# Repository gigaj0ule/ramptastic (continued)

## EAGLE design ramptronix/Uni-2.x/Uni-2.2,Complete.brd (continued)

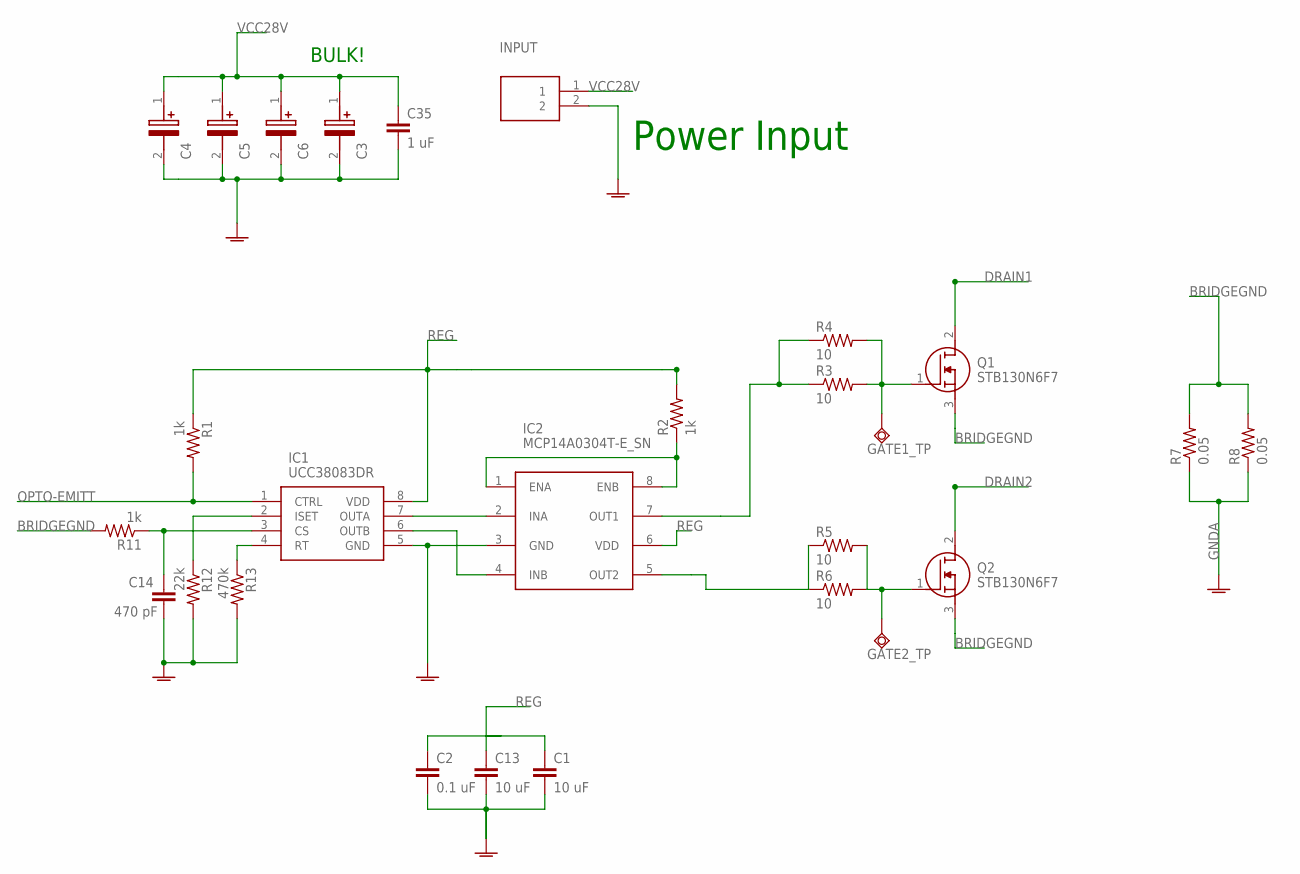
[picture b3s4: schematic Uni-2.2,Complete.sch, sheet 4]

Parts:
C1, C13: 10 uF; C0603K; LCSC_PART C440198
C2: 0.1 uF; C0603K; LCSC_PART C440198
C3, C4, C5, C6: OVK151M1VTR-10131; 16SVF1000M
C14: 470 pF; C0603K; LCSC_PART C1620
C35: 1 uF; C0805K; LCSC_PART C440198
GATE1_TP, GATE2_TP: TPSQPAD1-17; P1-17
IC1: UCC38083DR; SOIC127P600X175-8N
IC2: MCP14A0304T-E_SN; SOIC127P600X175-8N
INPUT: TB005-762-02BE; TB00576202BE
Q1, Q2: STB130N6F7; D2PAK
R1: 1k; R0603; LCSC_PART C22975
R2: 1k; R0402
R3, R4, R5, R6: 10; R0805
R7, R8: 0.05; R2512
R11: 1k; R0603; LCSC_PART C21190
R12: 22k; R0603; LCSC_PART C31850
R13: 470k; R0603; LCSC_PART C25811

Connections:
BRIDGEGND: Q1.3 (S), Q2.3 (S), R7.2, R8.2, R11.2
CS-IN: C14.1, IC1.3 (CS), R11.1
DRAIN1: Q1.2 (D); also elsewhere on the board
DRAIN2: Q2.2 (D); also elsewhere on the board
GNDA: C1.2, C2.2, C3.2 (-), C4.2 (-), C5.2 (-), C6.2 (-), C13.2, C14.2, C35.2, IC1.5 (GND), IC2.3 (GND), INPUT.2, R7.1, R8.1, R12.2, R13.2; also elsewhere on the board
unnamed: IC1.7 (OUTA), IC2.2 (INA)
unnamed: IC1.6 (OUTB), IC2.4 (INB)
unnamed: IC2.1 (ENA), IC2.8 (ENB), R2.1
unnamed: IC2.7 (OUT1), R3.1, R4.1
unnamed: IC2.5 (OUT2), R5.1, R6.1
unnamed: IC1.2 (ISET), R12.1
OPTO-EMITT: IC1.1 (CTRL), R1.2; also elsewhere on the board
Q1G: GATE1_TP.TP, Q1.1 (G), R3.2, R4.2
Q2G: GATE2_TP.TP, Q2.1 (G), R5.2, R6.2
REG: C1.1, C2.1, C13.1, IC1.8 (VDD), IC2.6 (VDD), R1.1, R2.2; also elsewhere on the board
RT: IC1.4 (RT), R13.1
VCC28V: C3.1 (+), C4.1 (+), C5.1 (+), C6.1 (+), C35.1, INPUT.1; also elsewhere on the board

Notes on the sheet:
BULK!
Power Input

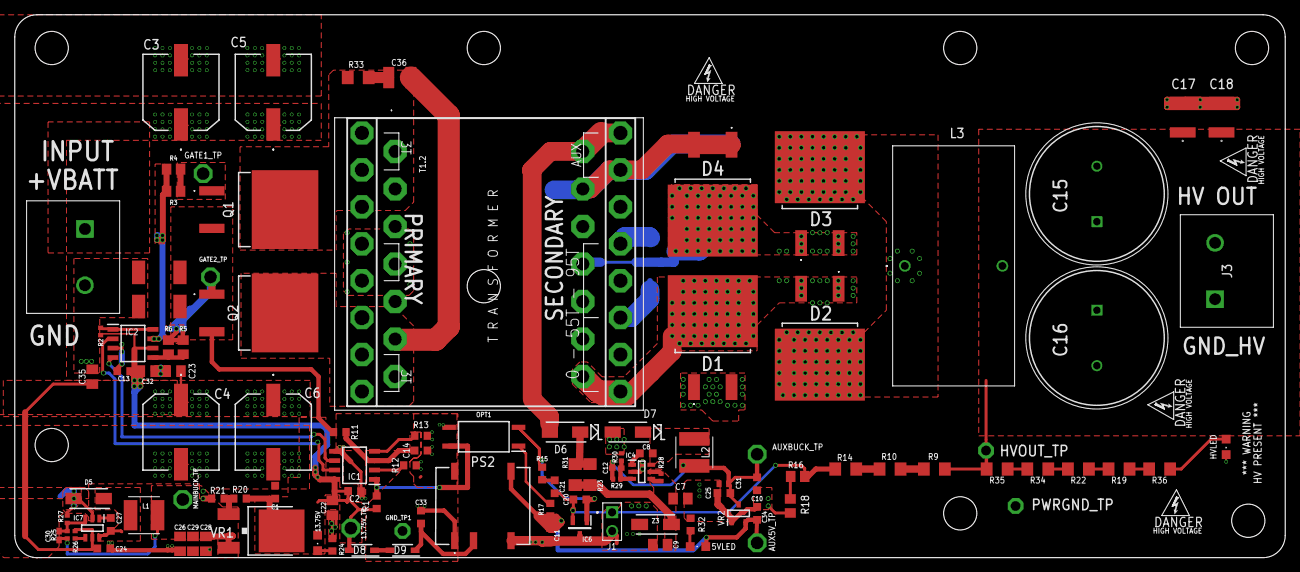
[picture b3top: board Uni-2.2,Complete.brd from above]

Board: 2 copper layers, 172.0 x 73.5 mm, 117 parts (1 on the bottom side), 56 nets.

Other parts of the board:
U$1, U$4: HV; PSFBC_ELECTRIC_SHOCK

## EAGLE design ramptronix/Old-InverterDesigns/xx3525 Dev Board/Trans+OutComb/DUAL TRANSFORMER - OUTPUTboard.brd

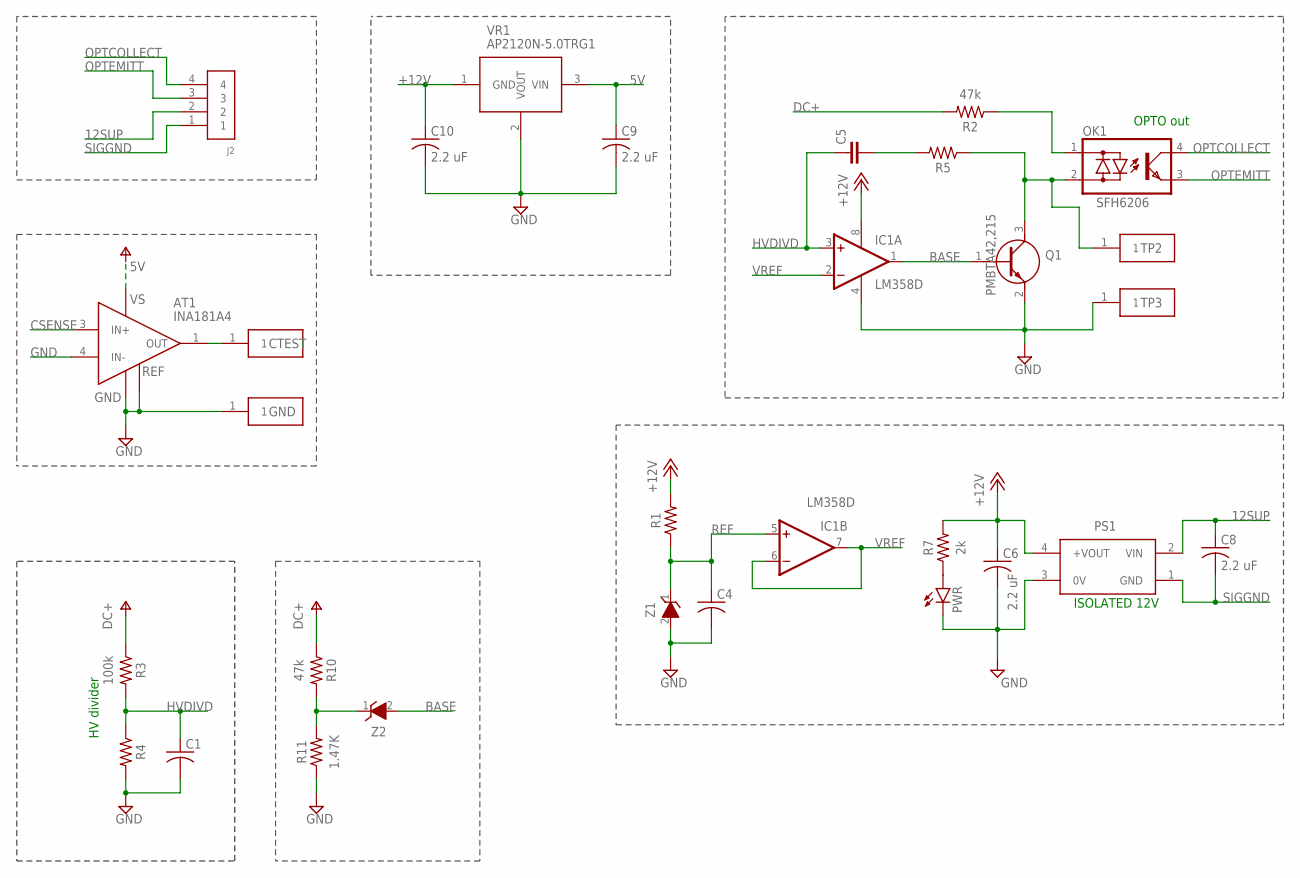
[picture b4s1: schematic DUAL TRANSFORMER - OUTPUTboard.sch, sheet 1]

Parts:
AT1: INA181A4; SOT95P280X145-6N
C1, C4: C-USC0805; C0805
C5: C-EUC0805; C0805
C6, C8, C9, C10: 2.2 uF; C0805
CTEST: RCT-0C
GND: RCT-0C
IC1: LM358D; SO08
J2: 61300411121
OK1: SFH6206; DIL4-SMD
PS1: PDSE1-S12-S3-SPDSE1S12S12S; PDSE1S12S3S
PWR: LEDSML0805; SML0805
Q1: PMBTA42,215; SOT95P230X110-3N
R1, R4, R5: R-US_CHIP-0805(2012-METRIC); RESC2012X65
R2, R10: 47k; MINI_MELF-0207R
R3: 100k; MINI_MELF-0207R
R7: 2k; RESC2012X65
R11: 1.47K; RESC2012X65
TP2, TP3: RCT-0C
VR1: AP2120N-5.0TRG1; SOT95P240X120-3N
Z1, Z2: BZT52-C5V1_R1_00001; SOD3816X135N; MOUSER_PART_NUMBER 241-BZT52C5V1

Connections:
5V: AT1.6 (VS), C9.1, VR1.3 (VIN)
12SUP: C8.1, J2.2, PS1.2 (VIN)
+12V: C6.1, C10.1, IC1.8 (V+), PS1.4 (+VOUT), R1.2, R7.2, VR1.1 (GND)
BASE: IC1.1 (OUT), Q1.1 (B), Z2.2 (A)
CSENSE: AT1.3 (IN+); also elsewhere on the board
DC+: R2.2, R3.1, R10.1; also elsewhere on the board
GND: AT1.2 (GND), AT1.4 (IN-), AT1.5 (REF), C1.2, C4.2, C6.2, C9.2, C10.2, GND.1, IC1.4 (V-), PS1.3 (0V), PWR.C, Q1.2 (E), R4.2, R11.1, TP3.1, VR1.2 (VOUT), Z1.2 (A); also elsewhere on the board
HVDIVD: C1.1, C5.1, IC1.3 (+IN), R3.2, R4.1
unnamed: PWR.A, R7.1
unnamed: R10.2, R11.2, Z2.1 (K)
unnamed: OK1.1 (AC1), R2.1
unnamed: C5.2, R5.2
unnamed: AT1.1 (OUT), CTEST.1
OPTCOLLECT: J2.4, OK1.4 (C)
OPTEMITT: J2.3, OK1.3 (E)
OPTOANODE: OK1.2 (AC2), Q1.3 (C), R5.1, TP2.1
REF: C4.1, IC1.5 (+IN), R1.1, Z1.1 (K)
SIGGND: C8.2, J2.1, PS1.1 (GND)
VREF: IC1.2 (-IN), IC1.6 (-IN), IC1.7 (OUT)

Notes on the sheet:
OPTO out
HV divider
ISOLATED 12V

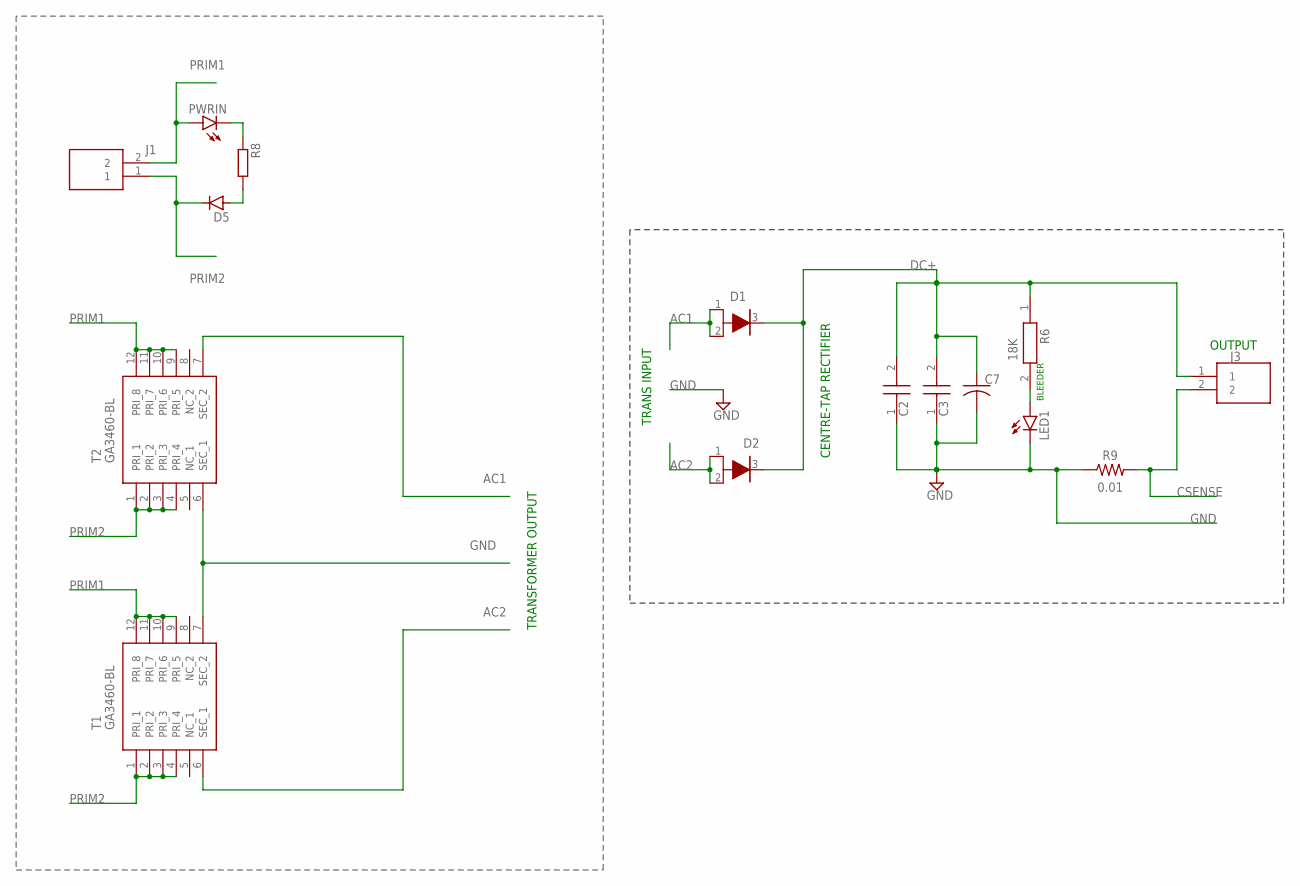
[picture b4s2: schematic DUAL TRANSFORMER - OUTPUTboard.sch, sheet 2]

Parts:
C2, C3: ELH227M400AS2AV; CAPPRD1000W140D3000H3200
C7: C-USC1210K; C1210K
D1, D2: VS-16EDH02HM3_I; V40DL45BPM3I
D5: DIODE-DO-214AC; DO-214AC
J1, J3: 2305908-2; 23059082
LED1: LED5MM
PWRIN: LEDSML0805; SML0805
R6: 18K; RESAD3100W80L1500D400
R8: R-EU_R0805; R0805
R9: 0.01; RESC6332X71
T1, T2: GA3460-BL; GA3460BL

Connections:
AC1: D1.1 (A_1), D1.2 (A), T2.7 (SEC_2)
AC2: D2.1 (A_1), D2.2 (A), T1.6 (SEC_1)
CSENSE: J3.2, R9.2; also elsewhere on the board
DC+: C2.2 (-), C3.2 (-), C7.1, D1.3 (K), D2.3 (K), J3.1, R6.1; also elsewhere on the board
GND: C2.1 (+), C3.1 (+), C7.2, LED1.K (C), R9.1, T1.7 (SEC_2), T2.6 (SEC_1); also elsewhere on the board
unnamed: D5.A, R8.2
unnamed: LED1.A, R6.2
unnamed: PWRIN.C, R8.1
PRIM1: J1.2, PWRIN.A, T1.9 (PRI_5), T1.10 (PRI_6), T1.11 (PRI_7), T1.12 (PRI_8), T2.9 (PRI_5), T2.10 (PRI_6), T2.11 (PRI_7), T2.12 (PRI_8)
PRIM2: D5.C, J1.1, T1.1 (PRI_1), T1.2 (PRI_2), T1.3 (PRI_3), T1.4 (PRI_4), T2.1 (PRI_1), T2.2 (PRI_2), T2.3 (PRI_3), T2.4 (PRI_4)

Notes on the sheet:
TRANSFORMER OUTPUT
CENTRE-TAP RECTIFIER
TRANS INPUT
OUTPUT
BLEEDER

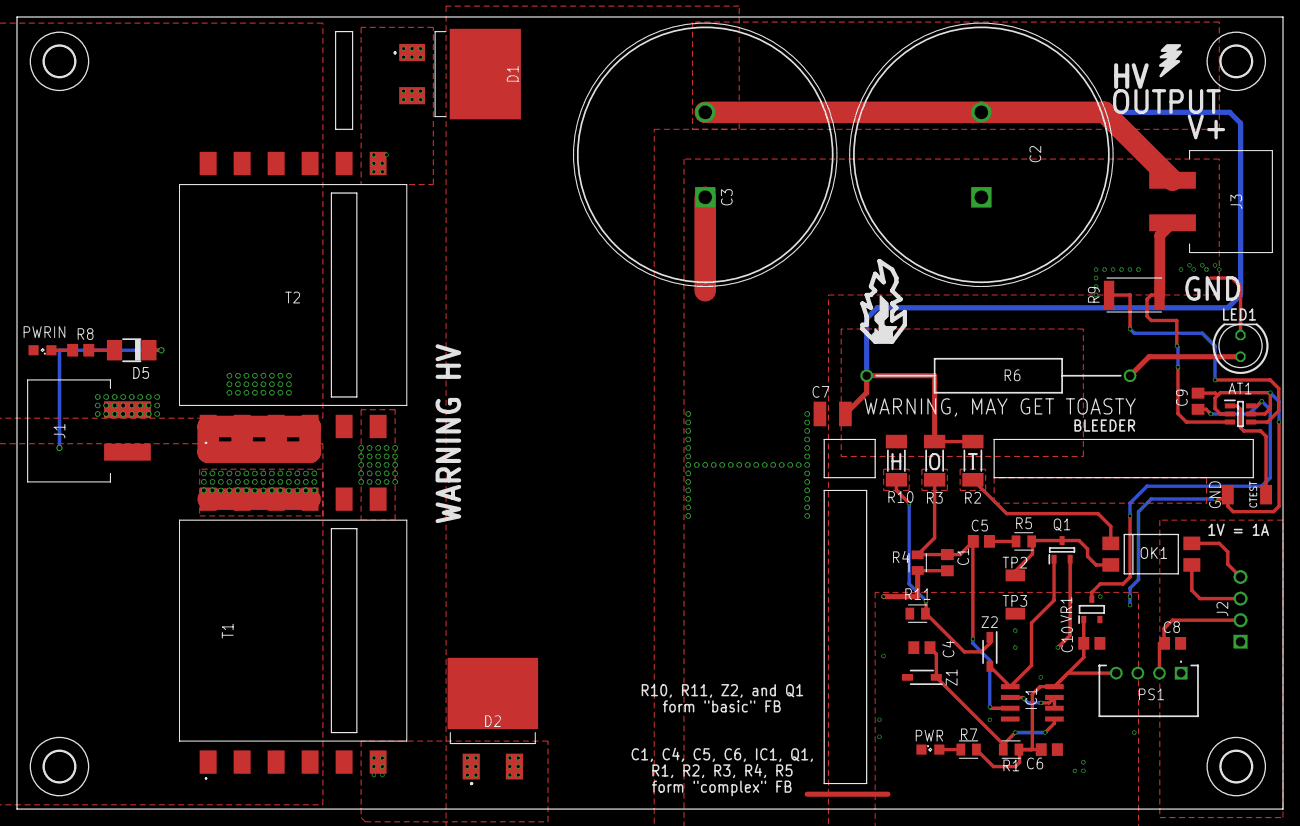
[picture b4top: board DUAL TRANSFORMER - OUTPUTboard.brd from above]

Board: 2 copper layers, 149.0 x 93.2 mm, 48 parts (0 on the bottom side), 26 nets.

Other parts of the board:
U$1, U$2, U$3, U$4: 3,6

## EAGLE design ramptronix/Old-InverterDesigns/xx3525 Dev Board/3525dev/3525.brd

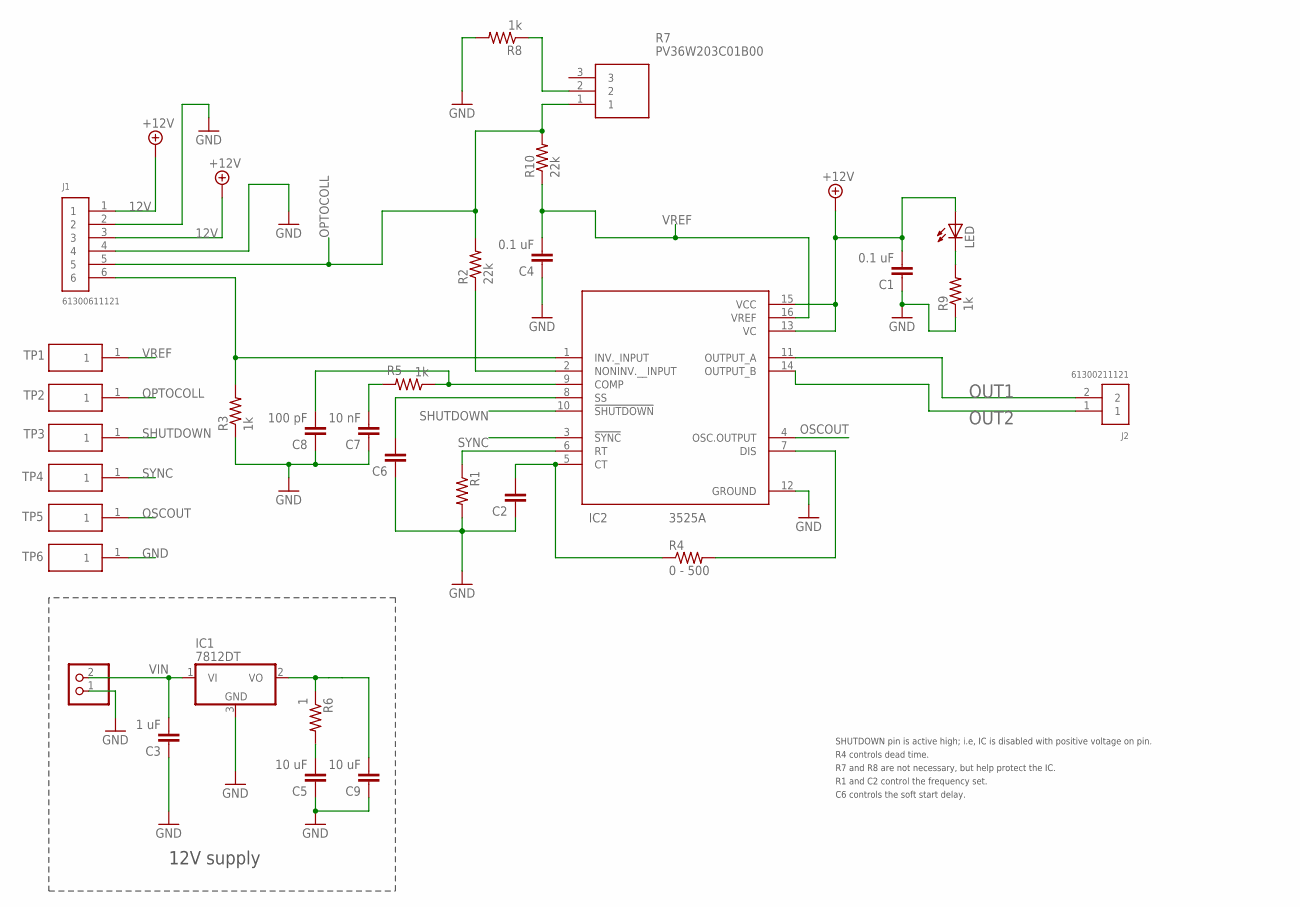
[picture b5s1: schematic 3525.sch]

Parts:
C1: 0.1 uF; C0805
C2, C6: C-EUC0805K; C0805K
C3: 1 uF; C0805K
C4: 0.1 uF; C0805K
C5, C9: 10 uF; C0805K
C7: 10 nF; C0805K
C8: 100 pF; C0805K
IC1: 7812DT; TO252
IC2: 3525A; SOIC127P1030X265-16N
J1: 61300611121
J2: 61300211121
LED: LEDCHIPLED_0805; CHIPLED_0805
R1: R-US_R0805; R0805
R2, R10: 22k; R0805
R3, R5, R8, R9: 1k; R0805
R4: 0 - 500; R0805
R6: 1; R0805
R7: PV36W203C01B00; PV36W201C01B00
SUPPLY: PINHD-1X2; 1X02
TP1, TP2, TP3, TP4, TP5, TP6: RCT-0C

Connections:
12V: C1.2, C9.2, IC1.2 (VO), IC2.13 (VC), IC2.15 (VCC), J1.1, J1.3, LED.A, R6.1
GND: C1.1, C2.1, C3.1, C4.1, C5.1, C6.1, C7.1, C8.1, C9.1, IC1.3 (GND), IC2.12 (GROUND), J1.2, J1.4, R1.2, R3.1, R8.2, R9.1, SUPPLY.1, TP6.1
unnamed: R7.2, R8.1
unnamed: C5.2, R6.2
unnamed: C8.2, IC2.9 (COMP), R5.1
unnamed: IC2.7 (DIS), R4.2
unnamed: IC2.6 (RT), R1.1
unnamed: C2.2, IC2.5 (CT), R4.1
unnamed: C6.2, IC2.8 (SS)
unnamed: LED.C, R9.2
unnamed: C7.2, R5.2
unnamed: IC2.1 (INV._INPUT), J1.6, R3.2
N-INV: IC2.2 (NONINV.__INPUT), R2.1
OPTOCOLL: J1.5, R2.2, R7.1, R10.2, TP2.1
OSCOUT: IC2.4 (OSC.OUTPUT), TP5.1
OUT1: IC2.11 (OUTPUT_A), J2.2
OUT2: IC2.14 (OUTPUT_B), J2.1
SHUTDOWN: IC2.10 (!SHUTDOWN), TP3.1
SYNC: IC2.3 (!SYNC), TP4.1
VIN: C3.2, IC1.1 (VI), SUPPLY.2
VREF: C4.2, IC2.16 (VREF), R10.1, TP1.1

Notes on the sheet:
12V supply
R4 controls dead time.
R7 and R8 are not necessary, but help protect the IC.
R1 and C2 control the frequency set.
C6 controls the soft start delay.
SHUTDOWN pin is active high; i.e, IC is disabled with positive voltage on pin.

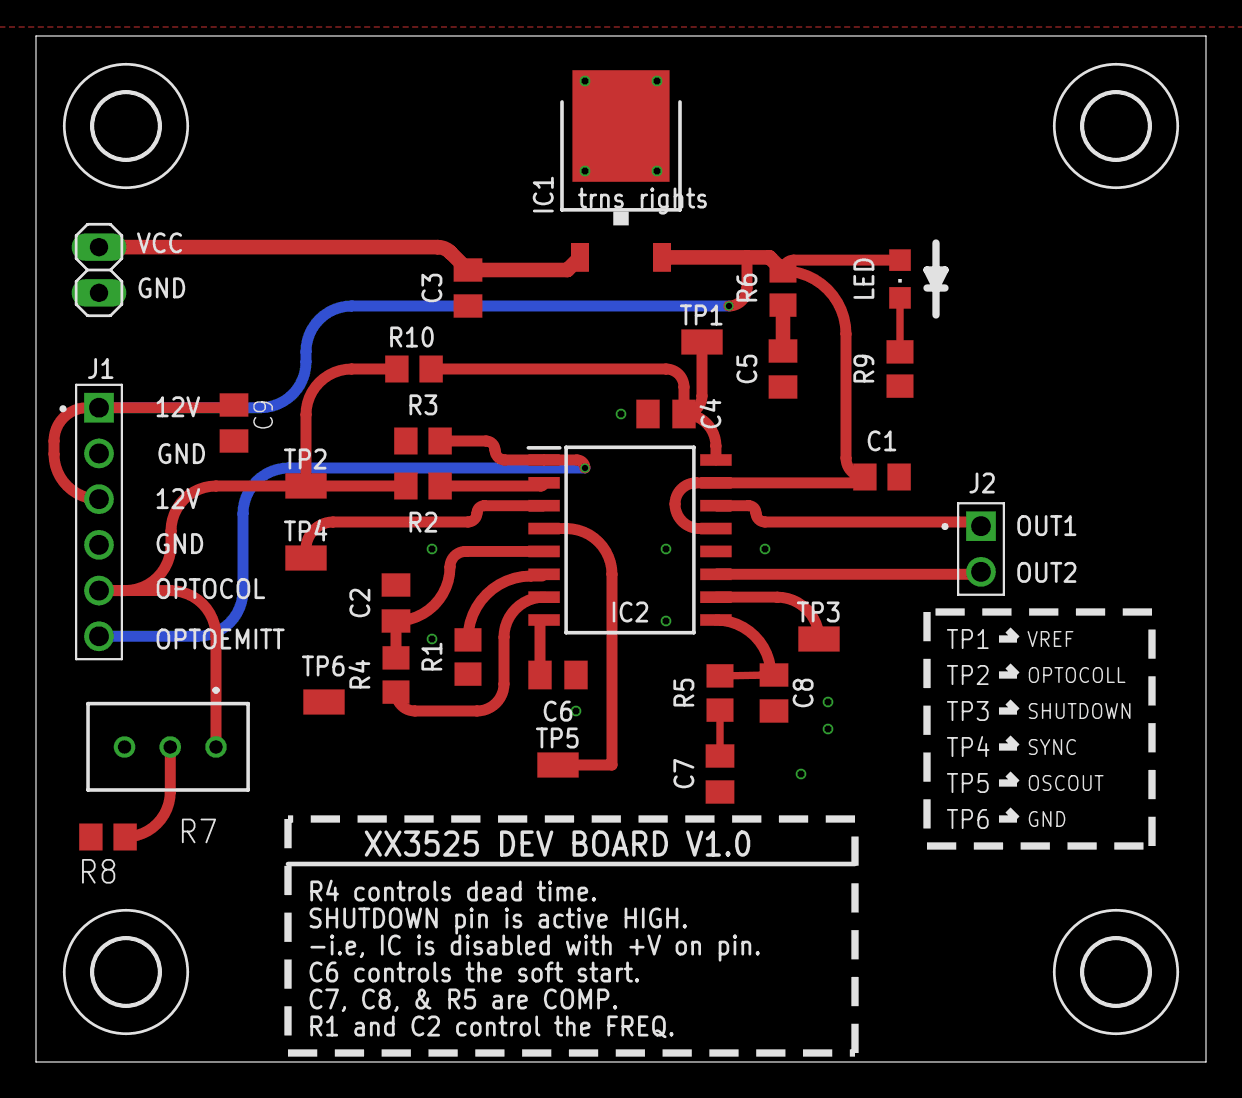
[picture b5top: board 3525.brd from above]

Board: 2 copper layers, 65.0 x 57.0 mm, 35 parts (0 on the bottom side), 21 nets.

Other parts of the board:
U$1, U$2, U$3, U$4: 3,6

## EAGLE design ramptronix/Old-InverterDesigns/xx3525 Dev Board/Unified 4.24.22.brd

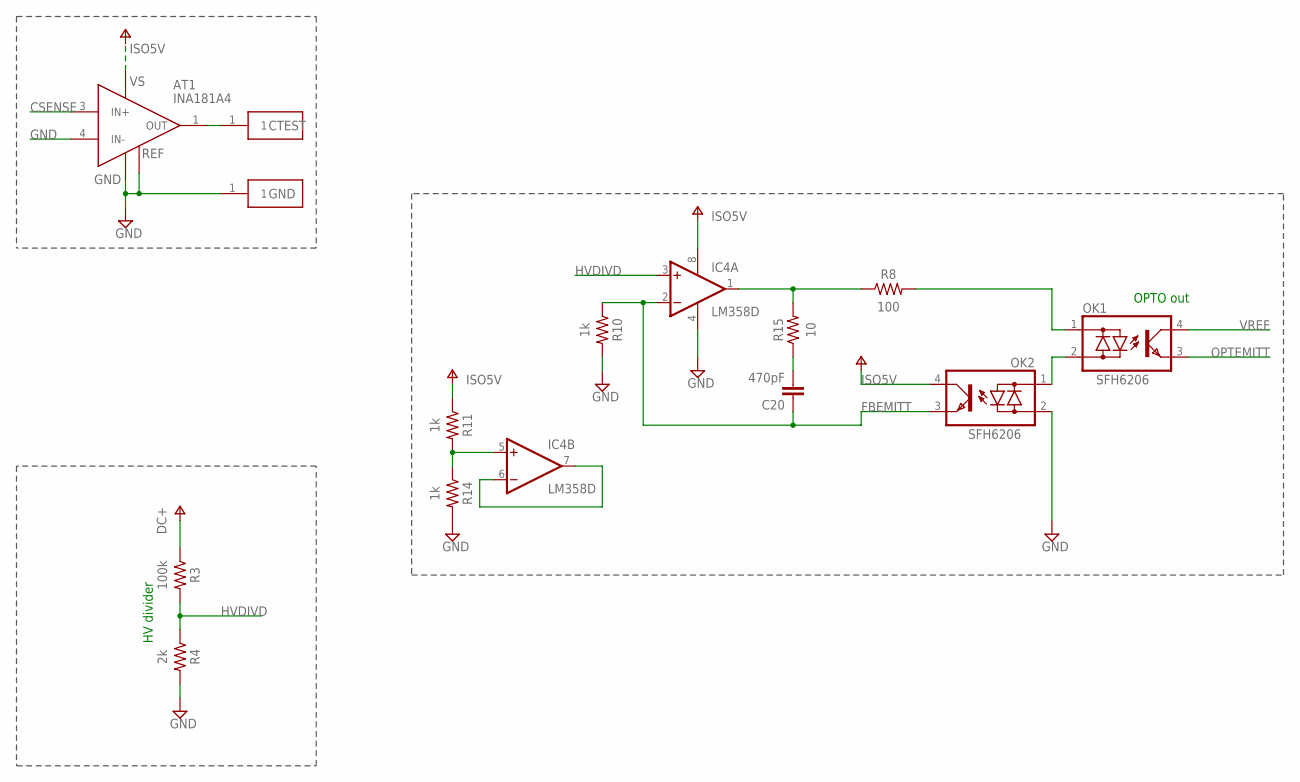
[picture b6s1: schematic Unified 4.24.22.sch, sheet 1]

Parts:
AT1: INA181A4; SOT95P280X145-6N
C20: 470pF; C0805K; LCSC_PART C1743
CTEST: RCT-0C
GND: RCT-0C
IC4: LM358D; SO08
OK1, OK2: SFH6206; DIL4-SMD
R3: 100k; MINI_MELF-0207R
R4: 2k; R0805
R8: 100; R0805
R10, R11, R14: 1k; R0805
R15: 10; R0805

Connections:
CSENSE: AT1.3 (IN+); also elsewhere on the board
DC+: R3.1; also elsewhere on the board
FBEMITT: C20.1, IC4.2 (-IN), OK2.3 (E), R10.1
GND: AT1.2 (GND), AT1.4 (IN-), AT1.5 (REF), GND.1, IC4.4 (V-), OK2.2 (AC2), R4.2, R10.2, R14.2; also elsewhere on the board
HVDIVD: IC4.3 (+IN), R3.2, R4.1
ISO5V: AT1.6 (VS), IC4.8 (V+), OK2.4 (C), R11.1; also elsewhere on the board
unnamed: OK1.1 (AC1), R8.2
unnamed: OK1.2 (AC2), OK2.1 (AC1)
unnamed: AT1.1 (OUT), CTEST.1
unnamed: IC4.5 (+IN), R11.2, R14.1
unnamed: IC4.1 (OUT), R8.1, R15.2
unnamed: IC4.6 (-IN), IC4.7 (OUT)
unnamed: C20.2, R15.1
OPTEMITT: OK1.3 (E); also elsewhere on the board
VREF: OK1.4 (C); also elsewhere on the board

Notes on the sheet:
OPTO out
HV divider

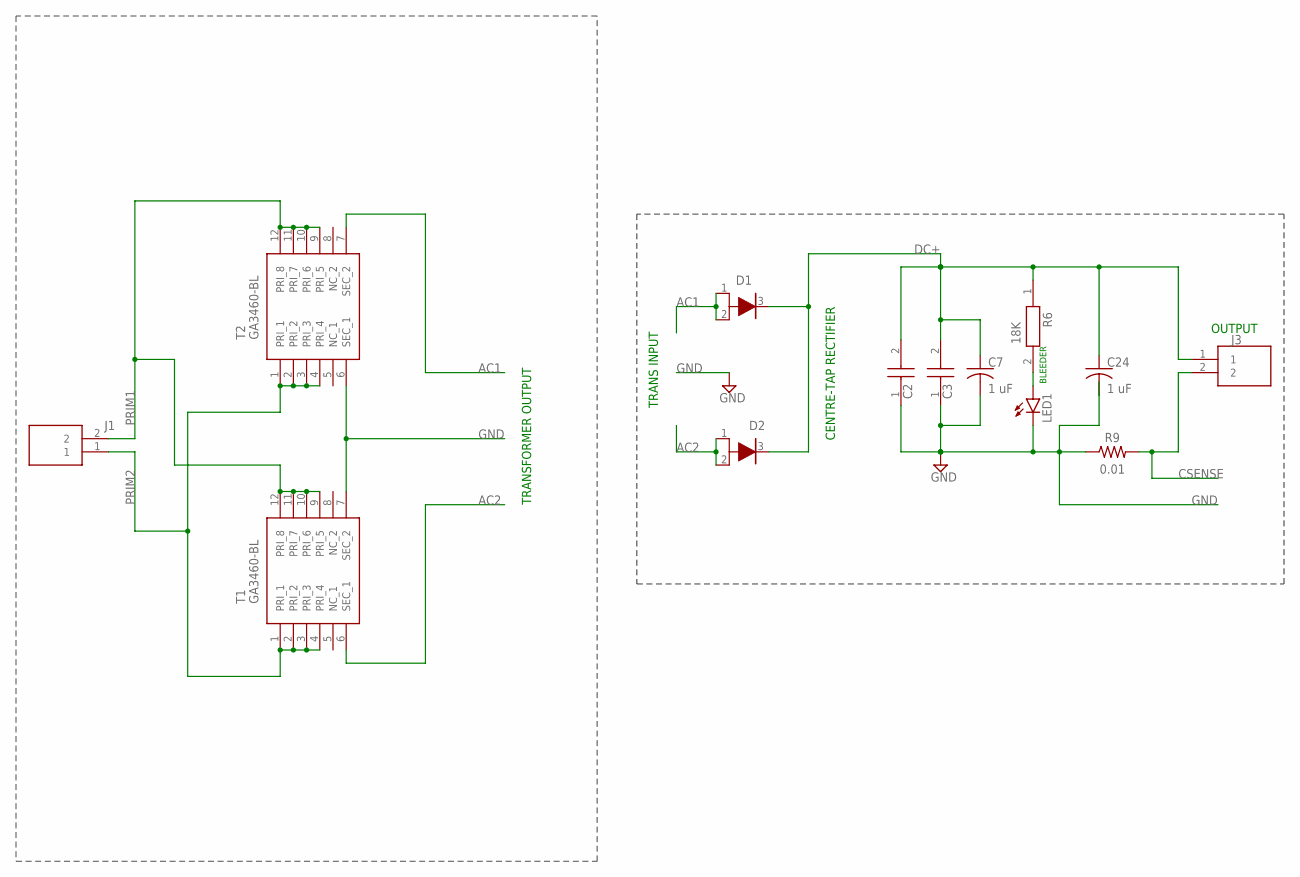
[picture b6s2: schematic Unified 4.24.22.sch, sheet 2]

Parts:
C2, C3: ELH227M400AS2AV; CAPPRD1000W140D3000H3200
C7, C24: 1 uF; C1210K
D1, D2: VS-16EDH02HM3_I; V40DL45BPM3I
J1, J3: 2305908-2; 23059082
LED1: LED5MM
R6: 18K; RESAD3100W80L1500D400
R9: 0.01; RESC6332X71
T1, T2: GA3460-BL; GA3460BL

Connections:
AC1: D1.1 (A_1), D1.2 (A), T2.7 (SEC_2)
AC2: D2.1 (A_1), D2.2 (A), T1.6 (SEC_1)
CSENSE: J3.2, R9.2; also elsewhere on the board
DC+: C2.2 (-), C3.2 (-), C7.1, C24.1, D1.3 (K), D2.3 (K), J3.1, R6.1; also elsewhere on the board
GND: C2.1 (+), C3.1 (+), C7.2, C24.2, LED1.K (C), R9.1, T1.7 (SEC_2), T2.6 (SEC_1); also elsewhere on the board
unnamed: LED1.A, R6.2
PRIM1: J1.2, T1.9 (PRI_5), T1.10 (PRI_6), T1.11 (PRI_7), T1.12 (PRI_8), T2.9 (PRI_5), T2.10 (PRI_6), T2.11 (PRI_7), T2.12 (PRI_8)
PRIM2: J1.1, T1.1 (PRI_1), T1.2 (PRI_2), T1.3 (PRI_3), T1.4 (PRI_4), T2.1 (PRI_1), T2.2 (PRI_2), T2.3 (PRI_3), T2.4 (PRI_4)

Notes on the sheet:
TRANSFORMER OUTPUT
CENTRE-TAP RECTIFIER
TRANS INPUT
OUTPUT
BLEEDER

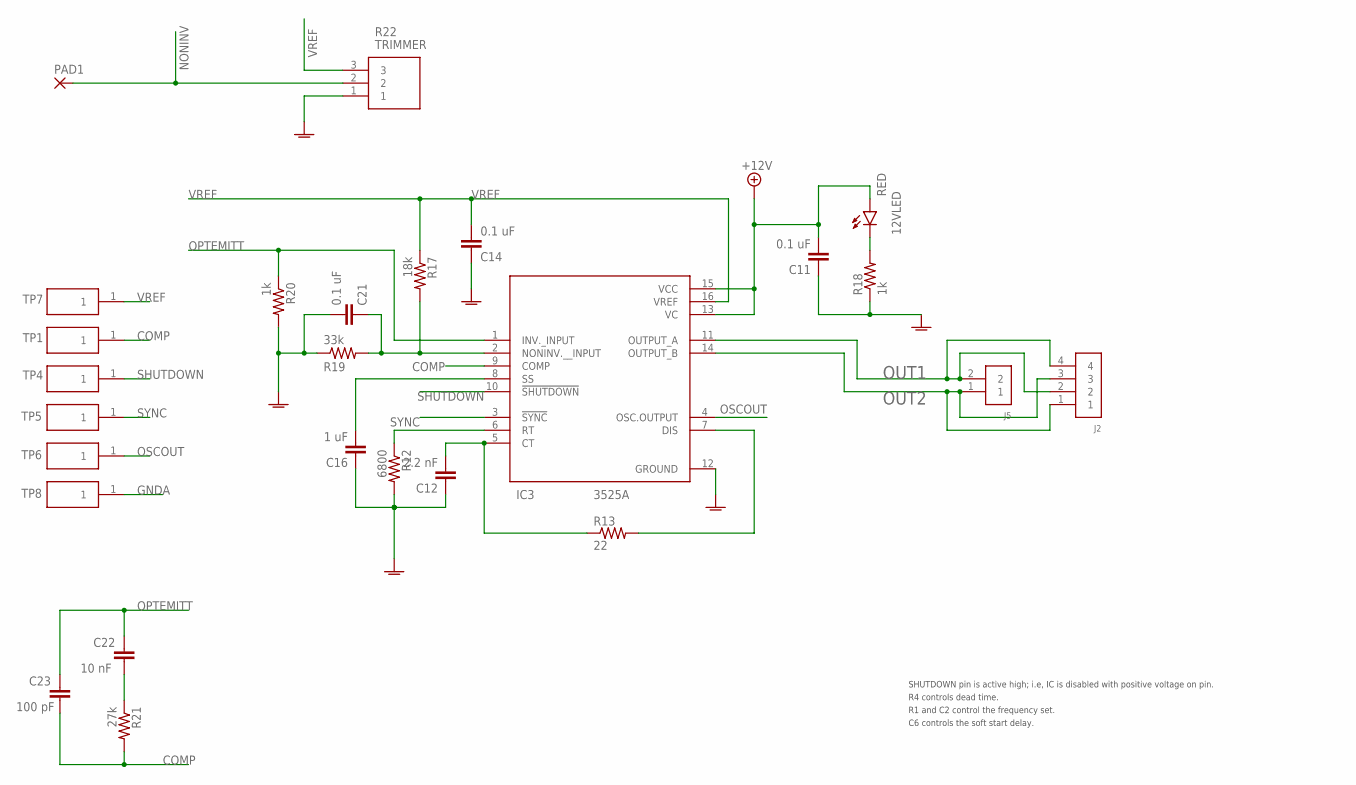
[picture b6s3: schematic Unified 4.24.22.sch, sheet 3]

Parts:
12VLED: RED; CHIPLED_0805
C11, C14, C21: 0.1 uF; C0805K; LCSC_PART C14663
C12: 2.2 nF; C0805K; LCSC_PART C1604
C16: 1 uF; C0805K; LCSC_PART C28323
C22: 10 nF; C0805K; LCSC_PART C1710
C23: 100 pF; C0805K; LCSC_PART C1790
IC3: 3525A; SOIC127P1030X265-16N
J2: 61300411121
J5: 61300211121
PAD1: 2,54/0,9
R12: 6800; R0805; LCSC_PART C17772
R13: 22; R0805; LCSC_PART C17561
R17: 18k; R0805; LCSC_PART C17506
R18, R20: 1k; R0805; LCSC_PART C17513
R19: 33k; R0805; LCSC_PART C17633
R21: 27k; R0805; LCSC_PART C17593
R22: TRIMMER; PV36W201C01B00
TP1, TP4, TP5, TP6, TP7, TP8: RCT-0C

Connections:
12V: 12VLED.A, C11.2, IC3.13 (VC), IC3.15 (VCC); also elsewhere on the board
COMP: C23.2, IC3.9 (COMP), R21.2, TP1.1
CT: C12.2, IC3.5 (CT), R13.1
DISCHARG: IC3.7 (DIS), R13.2
GNDA: C11.1, C12.1, C14.1, C16.1, C21.2, IC3.12 (GROUND), R12.2, R18.1, R19.1, R20.2, R22.1, TP8.1; also elsewhere on the board
unnamed: 12VLED.C, R18.2
unnamed: C22.2, R21.1
NONINV: C21.1, IC3.2 (NONINV.__INPUT), PAD1.1, R17.2, R19.2, R22.2
OPTEMITT: C22.1, C23.1, IC3.1 (INV._INPUT), R20.1; also elsewhere on the board
OSCOUT: IC3.4 (OSC.OUTPUT), TP6.1
OUT1: IC3.11 (OUTPUT_A), J2.2, J2.4, J5.2
OUT2: IC3.14 (OUTPUT_B), J2.1, J2.3, J5.1
RT: IC3.6 (RT), R12.1
SHUTDOWN: IC3.10 (!SHUTDOWN), TP4.1
SOFTSTART: C16.2, IC3.8 (SS)
SYNC: IC3.3 (!SYNC), TP5.1
VREF: C14.2, IC3.16 (VREF), R17.1, R22.3, TP7.1; also elsewhere on the board

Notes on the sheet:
R4 controls dead time.
R1 and C2 control the frequency set.
C6 controls the soft start delay.
SHUTDOWN pin is active high; i.e, IC is disabled with positive voltage on pin.

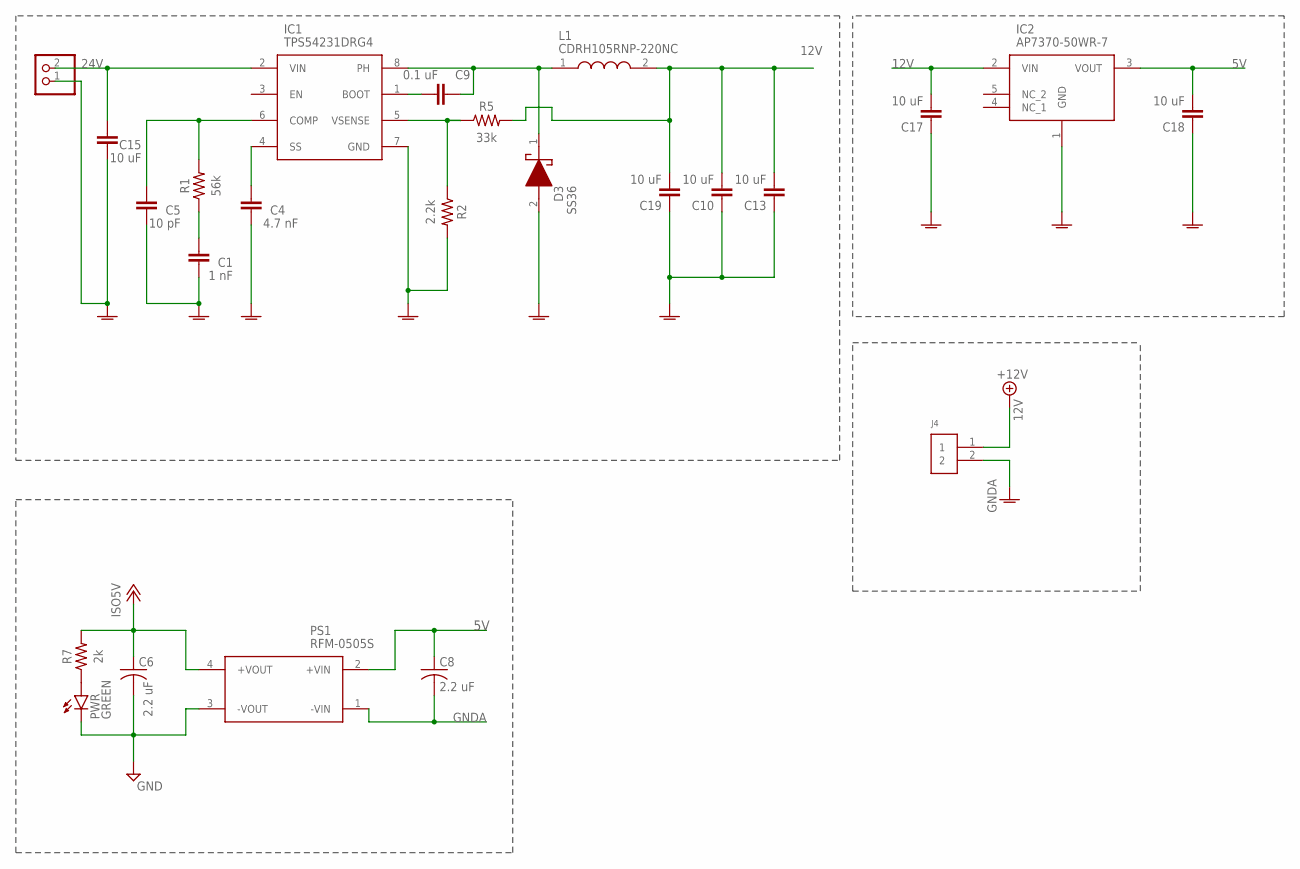
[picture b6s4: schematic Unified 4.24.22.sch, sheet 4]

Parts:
C1: 1 nF; C0805K; LCSC_PART C1588
C4: 4.7 nF; C0805K; LCSC_PART C53987
C5: 10 pF; C0805K; LCSC_PART C1785
C6, C8: 2.2 uF; C0805; LCSC_PART C23630
C9: 0.1 uF; C0805K; LCSC_PART C14663
C10, C13, C15, C17, C18, C19: 10 uF; C0805K; LCSC_PART C440198
D3: SS36; DIOM8059X265N
IC1: TPS54231DRG4; SOIC127P600X175-8N
IC2: AP7370-50WR-7; SOT95P285X140-5N
J4: 61300211121
L1: CDRH105RNP-220NC; INDPM102100X510N; LCSC_PART C225030
PS1: RFM-0505S; RFM0505S
PWR: GREEN; SML0805
R1: 56k; R0805
R2: 2.2k; R0805
R5: 33k; R0805
R7: 2k; R0805
SUPPLY: PINHD-1X2; 1X02

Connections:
5V: C8.1, C18.2, IC2.3 (VOUT), PS1.2 (+VIN)
12V: C10.2, C13.2, C17.2, C19.2, IC2.2 (VIN), J4.1, L1.2, R5.2; also elsewhere on the board
24V: C15.2, IC1.2 (VIN), SUPPLY.2
BOOT: C9.2, IC1.1 (BOOT)
GND: C6.2, PS1.3 (-VOUT), PWR.C; also elsewhere on the board
GNDA: C1.1, C4.1, C5.1, C8.2, C10.1, C13.1, C15.1, C17.1, C18.1, C19.1, D3.2 (A), IC1.7 (GND), IC2.1 (GND), J4.2, PS1.1 (-VIN), R2.2, SUPPLY.1; also elsewhere on the board
ISO5V: C6.1, PS1.4 (+VOUT), R7.2; also elsewhere on the board
unnamed: PWR.A, R7.1
unnamed: C1.2, R1.1
SWITCH: C9.1, D3.1 (K), IC1.8 (PH), L1.1
TPCOMP: C5.2, IC1.6 (COMP), R1.2
TPSS: C4.2, IC1.4 (SS)
VSEN: IC1.5 (VSENSE), R2.1, R5.1

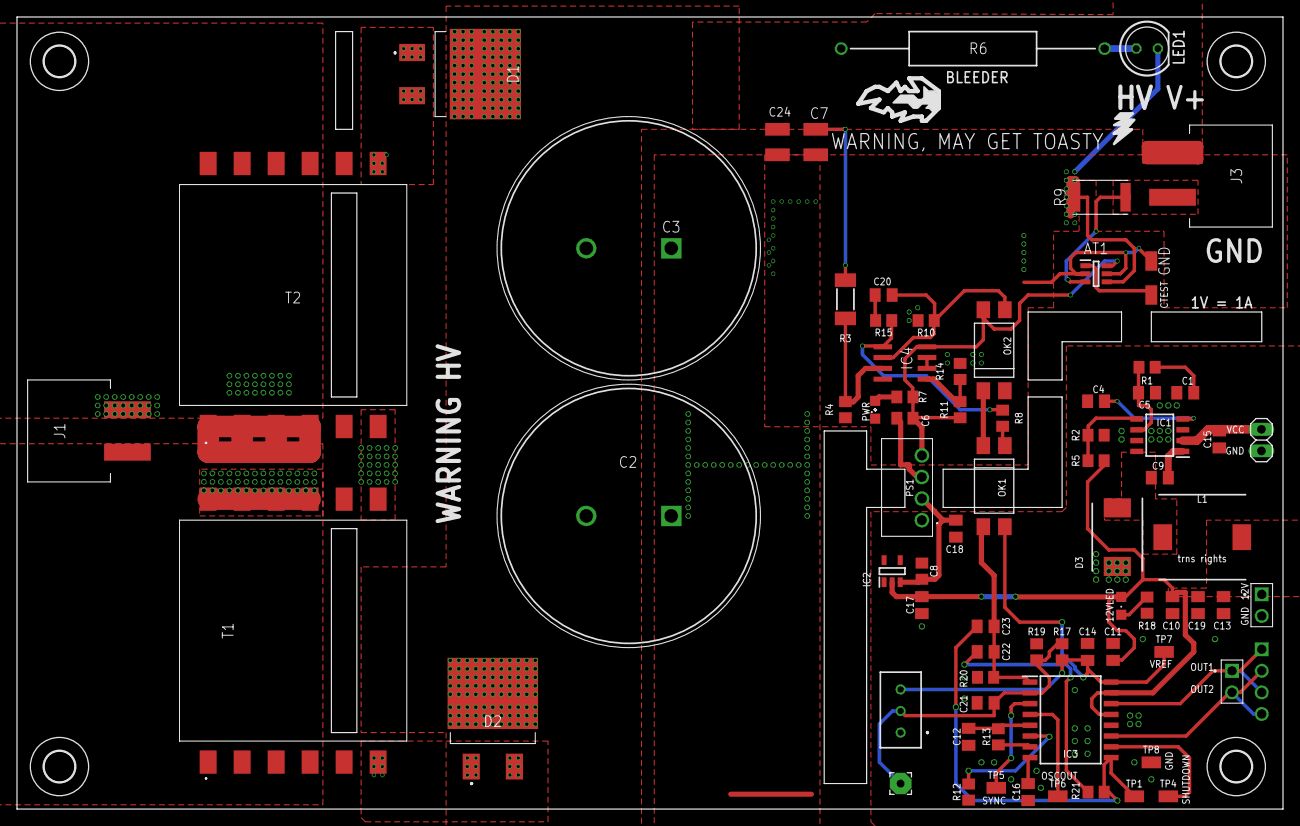
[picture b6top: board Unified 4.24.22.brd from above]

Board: 2 copper layers, 149.0 x 93.2 mm, 81 parts (0 on the bottom side), 44 nets.

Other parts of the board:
U$1, U$2, U$3, U$4: 3,6

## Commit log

2022-04-01 move to github
2022-04-08 add alec's stuff
2022-04-26 mosfet balancers
2022-05-17 new schem
2022-05-21 update again
2022-05-21 this commit still has rc filters
2022-06-21 ascii
2022-06-21 exports
2022-07-04 Adding Old Revisions, And New Revisions.
    Adding old inverter revisions that aren't being used presently. Also added new inverter board revisions, which, the newest as of typing is Uni-2.2.
2022-07-04 Uni-2.2 HW Design Update EAGLE
    Update
    - Hole patterns
    - LV Creapage/clearances
    - PWR Plane stitching via locations
    - PWR Plane routing
2022-07-05 Uni-2.3
    Misc Changes.
2022-07-09 Half Bridge - 0.0.2
    Half Bridge - 0.0.2
    Fixed net issue with OV clamp/crowbar
    Increased voltage rating of MOSFETs
    Increased voltage rating of CAPS
    Increased clearances for 400V operation
2022-07-21 Added Latest Board Revisions and Changelog.txt file
    see title
2022-08-20 Changelog update, and next rev of board
    see title
